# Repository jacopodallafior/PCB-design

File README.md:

# PCB-Design

This repository contains two PCB design projects, each focusing on sensor integration and signal processing. The designs were carried out using industry-standard tools and methodologies, ensuring robust performance in real-world applications.

### 1. Project 1 - Accelerometer PCB with Double LED Detection System
- **Project File:** `accelerometer-pcb-design`
- **Description:** This project involves designing a PCB for an accelerometer that utilizes a novel double LED technique to detect acceleration. The design compares light intensity variations caused by motion to measure acceleration. This approach is highly sensitive, making it suitable for detecting small positional changes.

- **Key Components:**
  - **Double LED System:** The LEDs act as optical sensors, where changes in the relative distance between them (due to acceleration) alter the received light signal. This allows for precise acceleration detection.
  - **Signal Gain:** The design incorporates a gain stage to clean and amplify the small voltage changes produced by the LEDs. A high-gain operational amplifier is used to improve the signal-to-noise ratio, ensuring accurate measurements while minimizing interference.

- **Theory Behind the Gain:**
  - Since the LED sensors produce a low output voltage, amplification is required to improve the signal-to-noise ratio. An operational amplifier is used with a gain factor determined by:
    \[
    V_{\text{out}} = A \times (V_{\text{in}} - V_{\text{ref}})
    \]
    Where \(A\) represents the amplifier’s gain and \(V_{\text{ref}}\) is the reference voltage, which stabilizes the system. Amplifying the signal enables downstream components like the ADC to measure the acceleration accurately.

---

### 2. Project 2 - Complete PCB Design with DC Motor Controller Integration
- **Project File:** `motor-controller-pcb-design`
- **Description:** This project involves the complete design of a PCB, including both the schematic and layout, to integrate various components such as a **DC motor controller**. The design aims to manage motor control for applications that require precise motion handling. The PCB integrates power management, motor control, and communication interfaces, ensuring stable and reliable performance in real-world conditions.

- **Circuit Design and Layout:**
  - **Two-Layer PCB Design**: The PCB was designed as a two-layer board to separate signal and power planes, minimizing interference. The top layer handles most of the power components, while the bottom layer is used for signal routing and communication lines.
  - **H-Bridge Layout**: The H-bridge configuration of the DC motor controller was carefully laid out to minimize resistance and power loss. Free vias were used to ensure stable ground connections and avoid issues with heat dissipation.
  - **Trace Routing**: Power traces were routed with greater width to handle higher current, while control signal traces were kept short to reduce noise. Decoupling capacitors were placed strategically close to key components to filter high-frequency noise.

- **Special Features:**
  - **Motor Direction Control**: The motor controller allows for dynamic control of motor direction by toggling the DIR pin through the microcontroller. The PCB includes dedicated pins for this purpose.
  - **PWM Speed Control**: By connecting the motor controller’s PWM input to the microcontroller, the design supports precise motor speed control. This allows the user to modulate the speed based on the application’s requirements.
  - **Overcurrent and Thermal Protection**: The motor controller includes built-in protection circuits to prevent damage from overcurrent or overheating, ensuring the durability of the design in demanding conditions.

This project focuses on delivering a reliable and efficient motor control system through meticulous PCB design, incorporating all the necessary components to handle power management, motor control, and system protection.

For more details on the design and implementation of the motor controller PCB, refer to the technical documentation included in this repository.

## Getting Started

1. **Clone the repository:**
   ```bash
   git clone https://github.com/jacopodallafior/PCB-design.git

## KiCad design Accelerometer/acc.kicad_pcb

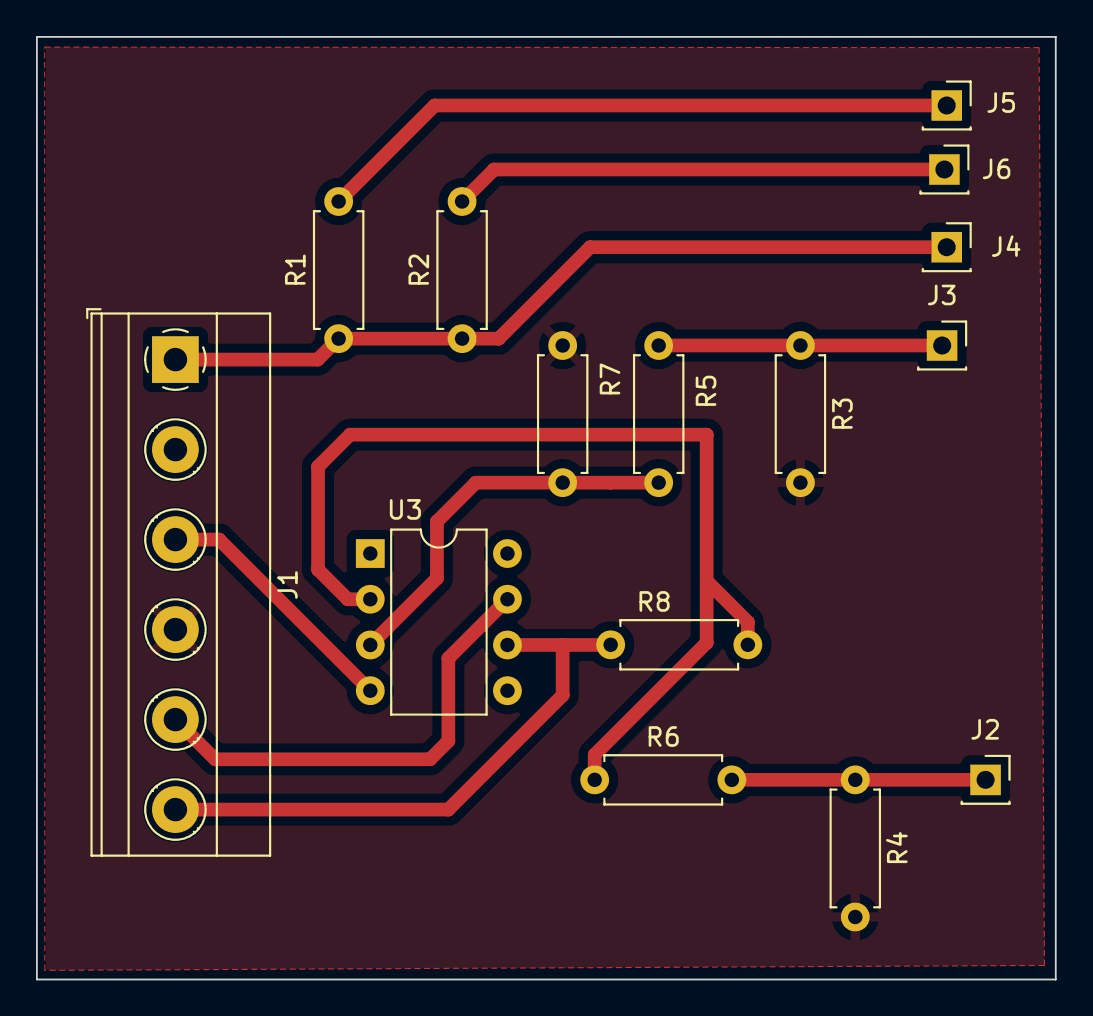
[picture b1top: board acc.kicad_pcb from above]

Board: 2 copper layers, 56.6 x 52.4 mm, 15 parts (0 on the bottom side), 11 nets.

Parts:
J1: Screw_Terminal_01x06; TerminalBlock_Phoenix_MKDS-1,5-6_1x06_P5.00mm_Horizontal
J2, J3, J4, J5, J6: Screw_Terminal_01x01; PinSocket_1x01_P2.54mm_Vertical
R1, R2: 350; R_Axial_DIN0207_L6.3mm_D2.5mm_P7.62mm_Horizontal
R3, R4: 1k; R_Axial_DIN0207_L6.3mm_D2.5mm_P7.62mm_Horizontal
R5, R6: 10k; R_Axial_DIN0207_L6.3mm_D2.5mm_P7.62mm_Horizontal
R7, R8: 100k; R_Axial_DIN0207_L6.3mm_D2.5mm_P7.62mm_Horizontal
U3: LM741; DIP-8_W7.62mm

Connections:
/5V: J1.1, J4.1, R1.1, R2.1
/+15V: J1.5, U3.7 (V+)
/-15V: J1.3, U3.4 (V-)
/OUT: J1.6, R8.1, U3.6
GND: J1.4, R3.2, R4.2, R7.1
unnamed: J5.1, R1.2
unnamed: J6.1, R2.2
unnamed: J2.1, R4.1, R6.2
unnamed: J3.1, R3.1, R5.1
unnamed: R5.2, R7.2, U3.3 (+)
unnamed: R6.1, R8.2, U3.2 (-)

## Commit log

2024-09-08 Create pcb
2024-09-08 Create Layout
